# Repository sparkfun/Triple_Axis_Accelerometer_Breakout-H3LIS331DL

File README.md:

SparkFun Triple Axis Accelerometer Breakout - H3LIS331DL
========================================

[*SparkFun Triple Axis Accelerometer Breakout - H3LIS331DL (SEN-14480)*](https://www.sparkfun.com/products/14480)

 This is a breakout board for the high-g H3LIS331DL three axis linear accelerometer. 
 The device has a digital I2C/SPI serial interface which makes it ideal for using in embedded applications. 
 All major pins are broken out to 0.1" spaced headers. It also includes four mounting holes as well.
 
Repository Contents
-------------------

* **/Firmware** - Example code 
* **/Hardware** - Eagle design files (.brd, .sch)
* **/Production** - Production panel files (.brd)

License Information
-------------------
This product is _**open source**_! 

The **hardware** is released under [Creative Commons ShareAlike 4.0 International](https://creativecommons.org/licenses/by-sa/4.0/).

The **code** is beerware; if you see me (or any other SparkFun employee) at the local, and you've found our code helpful, please buy us a round!

Please use, reuse, and modify these files as you see fit. Please maintain attribution to SparkFun Electronics and release anything derivative under the same license.

Distributed as-is; no warranty is given.

- Your friends at SparkFun.

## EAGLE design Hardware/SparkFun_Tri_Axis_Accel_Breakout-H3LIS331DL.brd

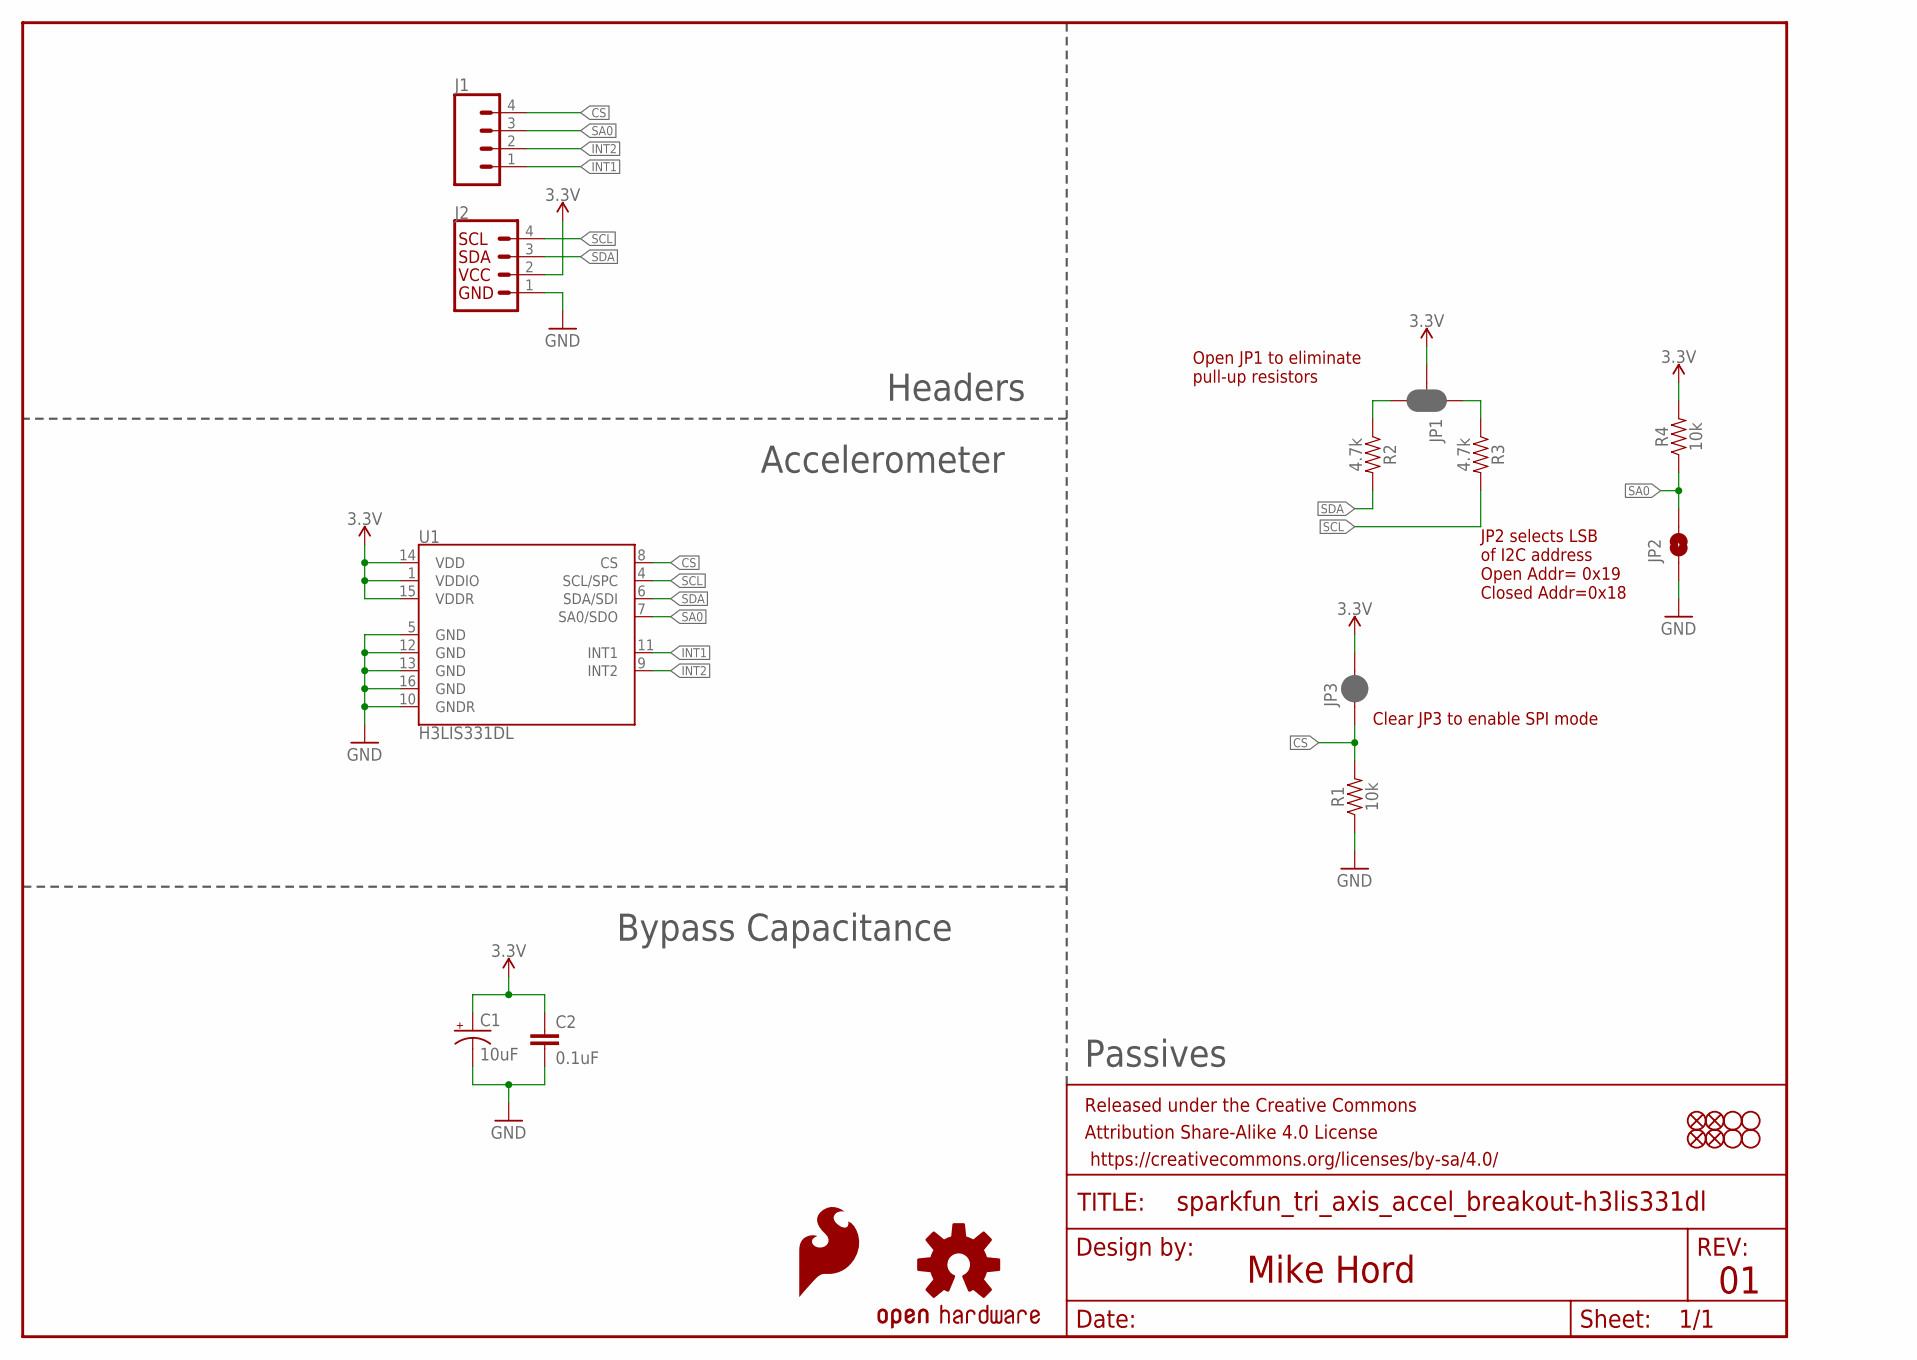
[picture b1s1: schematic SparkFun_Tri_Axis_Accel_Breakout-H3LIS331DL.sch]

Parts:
C1: 10uF; EIA3216
C2: 0.1uF; 0603
FRAME1: FRAME-LETTER; CREATIVE_COMMONS
J1: CONN_04; 1X04
J2: I2C_STANDARD; 1X04
JP1: JUMPER-SMT_3_2-NC_PASTE_NO-SILK; SMT-JUMPER_3_2-NC_PASTE_NO-SILK
JP2: JUMPER-SMT_2_NO_NO-SILK; SMT-JUMPER_2_NO_NO-SILK
JP3: JUMPER-SMT_2_NC_PASTE_NO-SILK; SMT-JUMPER_2_NC_PASTE_NO-SILK
JP4, JP5, JP6, JP7: FIDUCIAL1X2; FIDUCIAL-1X2
JP8, JP9, JP10, JP11: STAND-OFF
LOGO1: SFE_LOGO_FLAME.1_INCH; SFE_LOGO_FLAME_.1
LOGO2: OSHW-LOGOS; OSHW-LOGO-S
R1, R4: 10k; 0603
R2, R3: 4.7k; 0603
U1: H3LIS331DL; LGA-16-3X3

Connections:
3.3V: C1.+, C2.1, J2.2, JP1.2, JP3.2, R4.2, U1.1 (VDDIO), U1.14 (VDD), U1.15 (VDDR)
CS: J1.4, JP3.1, R1.2, U1.8 (CS)
GND: C1.-, C2.2, J2.1, JP2.1, R1.1, U1.5 (GND), U1.10 (GNDR), U1.12 (GND), U1.13 (GND), U1.16 (GND)
INT1: J1.1, U1.11 (INT1)
INT2: J1.2, U1.9 (INT2)
unnamed: JP1.1, R3.1
unnamed: JP1.3, R2.1
SA0: J1.3, JP2.2, R4.1, U1.7 (SA0/SDO)
SCL: J2.4, R3.2, U1.4 (SCL/SPC)
SDA: J2.3, R2.2, U1.6 (SDA/SDI)

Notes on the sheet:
Mike Hord
Open JP1 to eliminate pull-up resistors
JP2 selects LSB of I2C address Open Addr= 0x19 Closed Addr=0x18
Clear JP3 to enable SPI mode
Headers
Accelerometer
Bypass Capacitance
Passives

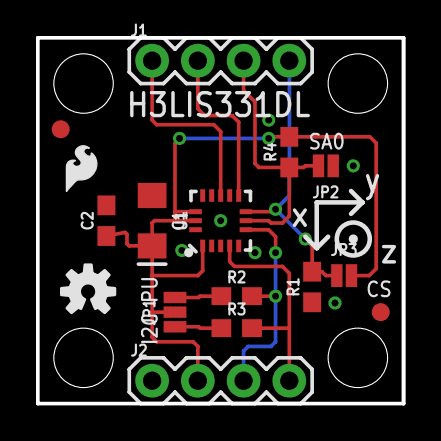
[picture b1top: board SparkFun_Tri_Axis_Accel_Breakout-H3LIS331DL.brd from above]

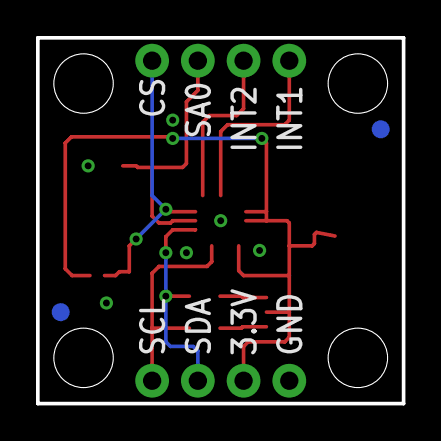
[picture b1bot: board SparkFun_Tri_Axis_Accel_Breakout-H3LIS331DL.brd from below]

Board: 2 copper layers, 20.3 x 20.3 mm, 23 parts (2 on the bottom side), 10 nets.

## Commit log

2017-08-16 Derived from LIS331 repository
2017-08-16 Add new design files
2017-09-11 Aesthetic touch ups before review
2017-09-11 Replace some components with newer versions
2017-09-12 Modified I2C address jumper note
2017-09-14 Improvements post review
2017-09-19 panel
2017-12-22 Fixed typos in readme

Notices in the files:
parts and their libraries:
SparkFun-Sensors: Licensing: Creative Commons ShareAlike 4.0 International - https://creativecommons.org/licenses/by-sa/4.0
SparkFun-Aesthetics: Released under the Creative Commons Attribution Share-Alike 4.0 License
SparkFun-Aesthetics: Released under the Creative Commons
